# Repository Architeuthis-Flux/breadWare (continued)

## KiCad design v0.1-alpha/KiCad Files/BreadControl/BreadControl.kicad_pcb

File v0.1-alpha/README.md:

# breadWare v0.1

Hey guys, here's the PCB layout for the switch matrix board. Those holes should line up with the columns on a breadboard so this whole thing can be soldered directly onto the bottom. I just ordered 10 of these boards (in red soldermask! I've never been patient enough to wait the extra 24-48 hours to do a color other than green) so we can put a few together (I can teach whoever's interested how to hot air solder these surface mount parts) and then get on making those header pins on the sides move the correct number of electrons to make this thing work.

#
 
That white rectangle is roughly the size of a breadboard. We might be able to get the size down if we use [TQFP](https://en.wikipedia.org/wiki/Quad_flat_package) instead of these huge [PLCC](https://en.wikipedia.org/wiki/Chip_carrier#Plastic-leaded_chip_carrier) sockets. Also could someone who reads chinese look through [this datasheet](https://datasheet.lcsc.com/szlcsc/Jiangsu-Qin-Heng-CH446Q_C109471.pdf) for the [CH446Q](http://www.wch-ic.com/products/CH446.html) and tell me if there are any significant differences from [MT8816](http://images.100y.com.tw/pdf_file/41-ZARLINK-MT8816.pdf) that we're using? Because the [JLCPCB](https://jlcpcb.com/) (who is making these boards for us) has the CH446Q in stock and they'll make the board and then solder them on so we can just order fully assembled boards ridiculously cheap (and the chips themselves are ~$1, so like a quarter of the price.)

#
 
Notice how some of the pads in the middle (Plated Through Holes or PTH is the correct term just so you know) are more square and others are rounded. The squarer ones means that that pin is connected to the headers on the sides, so it can be used for measurement or power or whatever we decide when we make the control board. Those pins are: 0,1,8,16,24,31,32,40,48,56,63 which is the Y0 pin on each chip plus the ones that end up on the edges of the breadboard (31,63) and 1 because I had an extra header pin available. 
Pin 0 is connected to the Negative rail on the top of the breadboard, 31 is the top Positive rail, 32 is the bottom Negaitve rail, and 63 is the bottom Positive rail. Everything else is where you'd expect it to be.

#
 
Yes, these pin headers are on the wrong side but I'm not gonna let some stupid auto-generated 3D model tell me which side to solder them on. I might spend some time finding the 3D models for the PLCC sockets and a breadboard so this looks closer to the real thing.
Also, notice the silkscreened lines on the top and bottom are just a bit off from the holes, turns out the power rails on a breadboard arent spaced perfectly on the same grid as the rest of the pins. The line is marked where it would be if the universe made any sense.

#
 
Those letters along the middle correspond to the row labels on a breadboard.

#
  
Here's a zoomed out view of the whole schematic, those blue lines are busses, so they're actually 4 wires bundled together to make it look less messy. This is following JJ's brilliant idea for how to connect everything except I looped the ends back around so they conceptually should be thought of as a ring, If someone wants to map that out on one of those [Ring Lattice Graphs](https://i.imgur.com/oiiyKlz.png), it might make all this easier to visualize.

#

On the left we have the address lines, control lines and power input. Except for the last three with numbers, these are connected to all 8 chips together, so to make just the one we want to control do stuff, we use the Chip Select lines on the right side (labeled CS_A-H) which are wired to each chip individually. If the CS is logic 0 (~0 Volts, LOW, whatever), that chip will ignore everything that's put on the address and control lines because that signal isn't meant for it and these chips ain't no eavesdroppin' bitches. (just for everyone's learning, Chip Select lines seem to almost always be Active Low, meaning they'll ignore everything when that pin is held at logic 1 (5V or 3.3V depending on the chip) which is denoted with a line above, C̅S̅ (or /CS because overlining text is a pain in the ass on a computer. and it's typically spoken as "bar", so "CS Bar" in this case) this chip is unusual because it's Active High.)

#
 
Here's a zoomed part so you can see how I named these interconnects, it goes Pin Name (X0, X1, etc.) then the letters of the two chips it's connecting (in alpabetical order). So the pin labeled X0CD connects pin X0 on chip C to pin X0 on chip D. I had to do this like 5 times to get the wires to always connect to the same pin on both chips, but it should make the software much easier to deal with. 

#
  
Here's the table I used to figure out which chips are connected where, and this helped me put them all in alphabetical order (because I can't tell you if F is before or after H without singing the alpabet song in my head every time) so the labels are the same on both sides of the wire. Each chip is connected the to the two before and after it. 

#
One day we will have this piece of paper framed and signed by JJ.

Here are some pictures of both boards after assembly:

That green board hanging off is 2 charge pumps in parallel (for added current handling, but it was probably unnecessary) and an LM337 Negative Voltage Regulator. I built that because the power rails weren't working until I realized I swapped Vss and Vee.

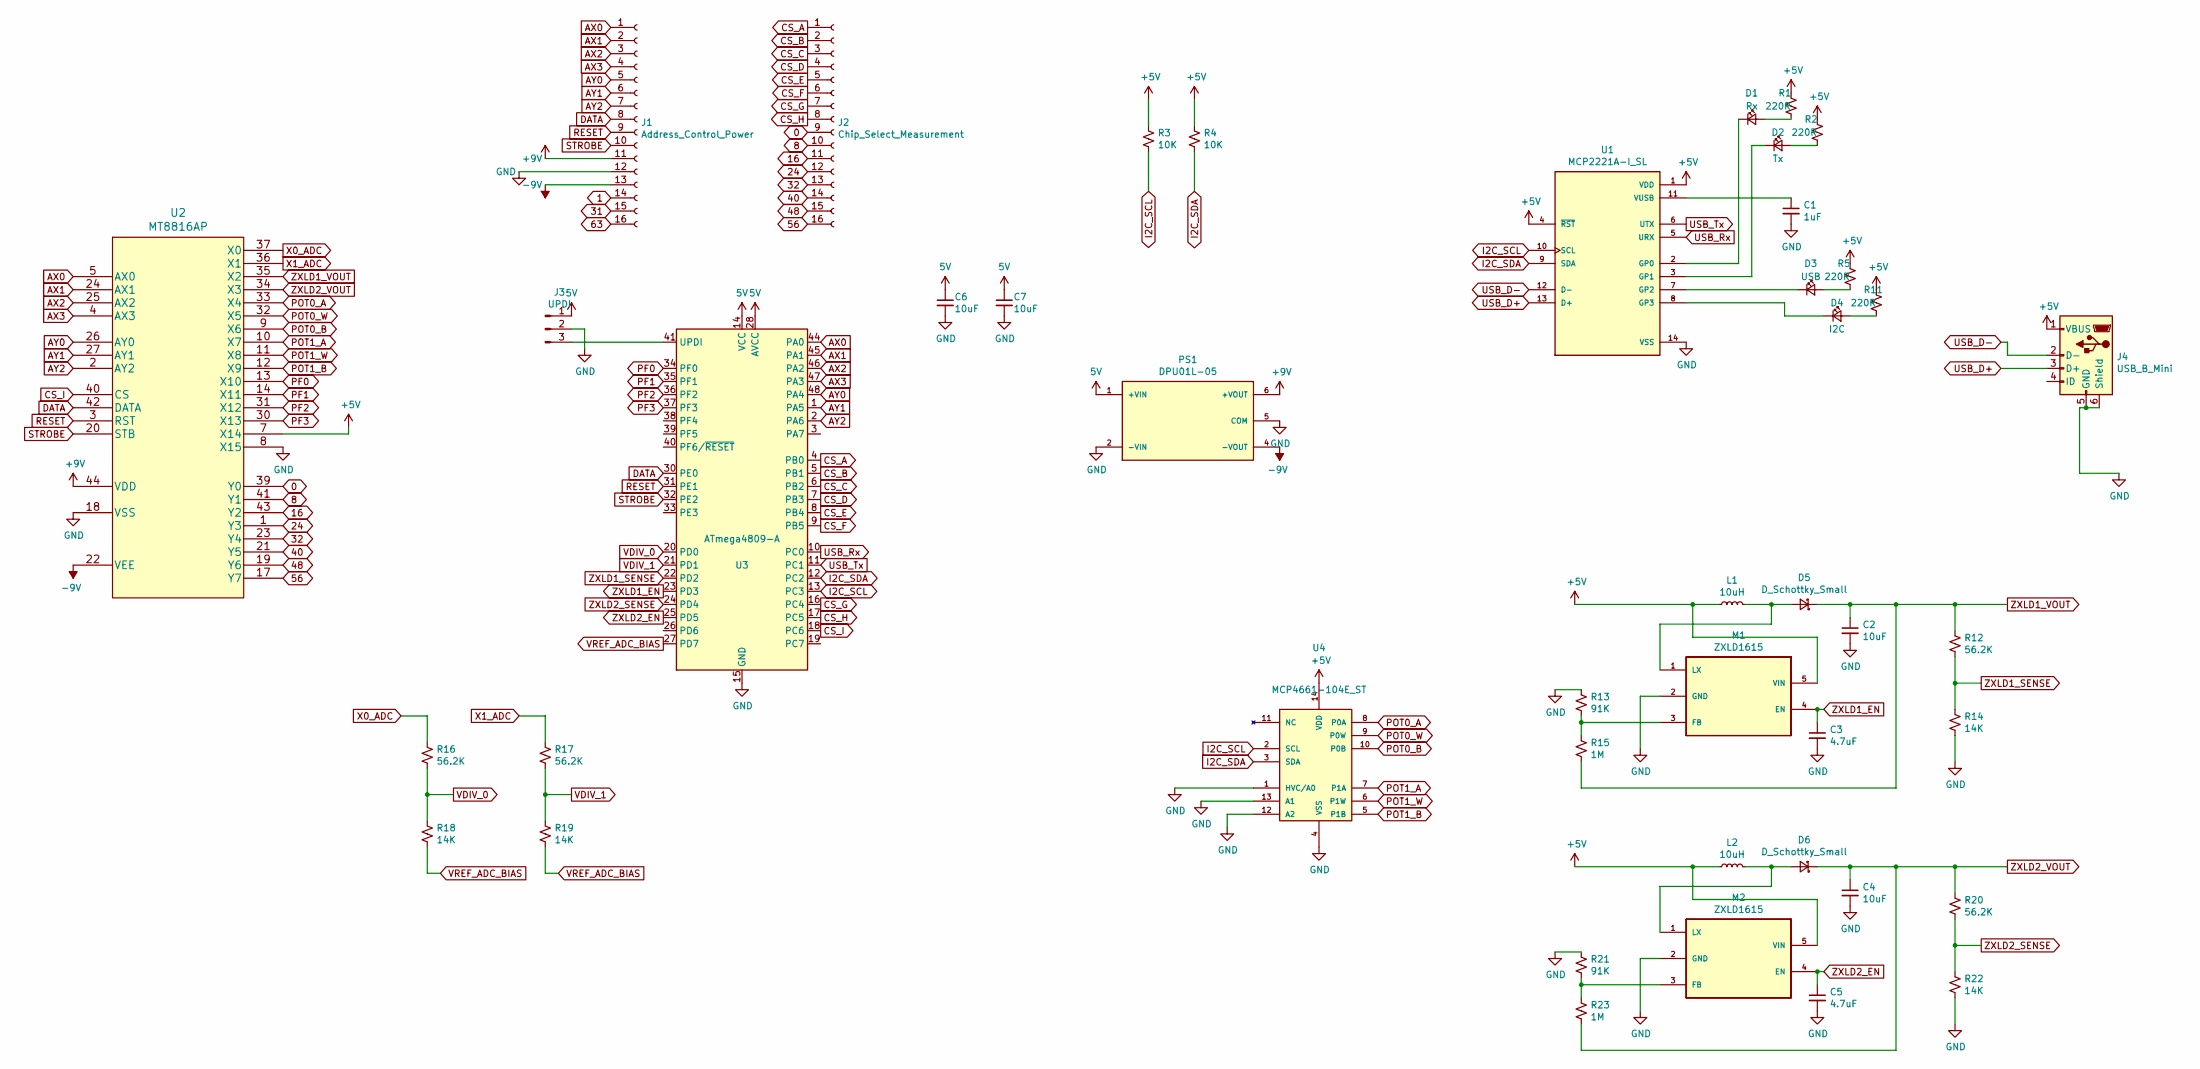
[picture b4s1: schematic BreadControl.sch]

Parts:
C1: 1uF; C_0805_2012Metric_Pad1.15x1.40mm_HandSolder
C2, C4, C6, C7: 10uF; C_0805_2012Metric_Pad1.15x1.40mm_HandSolder
C3, C5: 4.7uF; C_0805_2012Metric_Pad1.15x1.40mm_HandSolder
D1: Rx; D_0603_1608Metric_Pad1.05x0.95mm_HandSolder
D2: Tx; D_0603_1608Metric_Pad1.05x0.95mm_HandSolder
D3: USB; D_0603_1608Metric_Pad1.05x0.95mm_HandSolder
D4: I2C; D_0603_1608Metric_Pad1.05x0.95mm_HandSolder
D5, D6: D_Schottky_Small; D_SOD-323_HandSoldering
J1: Address_Control_Power; PinHeader_1x16_P2.54mm_Vertical
J2: Chip_Select_Measurement; PinHeader_1x16_P2.54mm_Vertical
J3: UPDI; PinHeader_1x03_P2.54mm_Vertical
J4: USB_B_Mini; AMPHENOL_10033526-N3212LF
L1, L2: 10uH; L_1008_2520Metric
M1, M2: ZXLD1615; SOT-23-5_HandSoldering
PS1: DPU01L-05; CONV_DPU01L-05; PARTREV 2017-03-06
R1, R2, R5, R11: 220R; R_0805_2012Metric_Pad1.15x1.40mm_HandSolder
R3, R4: 10K; R_0805_2012Metric_Pad1.15x1.40mm_HandSolder
R12, R16, R17, R20: 56.2K; R_0805_2012Metric_Pad1.15x1.40mm_HandSolder
R13, R21: 91K; R_0805_2012Metric_Pad1.15x1.40mm_HandSolder
R14, R18, R19, R22: 14K; R_0805_2012Metric_Pad1.15x1.40mm_HandSolder
R15, R23: 1M; R_0805_2012Metric_Pad1.15x1.40mm_HandSolder
U1: MCP2221A-I_SL; SOIC-14_3.9x8.7mm_P1.27mm
U2: MT8816AP; PLCC-44_16.6x16.6mm_P1.27mm
U3: ATmega4809-A; TQFP-48_7x7mm_P0.5mm
U4: MCP4661-104E_ST; TSSOP-14_4.4x5mm_P0.65mm; MPN MCP4661-104E/ST

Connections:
0: J2.9, U2.39 (Y0)
1: J1.14
8: J2.10, U2.41 (Y1)
16: J2.11, U2.43 (Y2)
24: J2.12, U2.1 (Y3)
31: J1.15
32: J2.13, U2.23 (Y4)
40: J2.14, U2.21 (Y5)
48: J2.15, U2.19 (Y6)
56: J2.16, U2.17 (Y7)
63: J1.16
+9V: J1.11, PS1.6 (+VOUT), U2.44 (VDD)
-9V: J1.13, PS1.4 (-VOUT), U2.22 (VEE)
AX0: J1.1, U2.5 (AX0), U3.44 (PA0)
AX1: J1.2, U2.24 (AX1), U3.45 (PA1)
AX2: J1.3, U2.25 (AX2), U3.46 (PA2)
AX3: J1.4, U2.4 (AX3), U3.47 (PA3)
AY0: J1.5, U2.26 (AY0), U3.48 (PA4)
AY1: J1.6, U2.27 (AY1), U3.1 (PA5)
AY2: J1.7, U2.2 (AY2), U3.2 (PA6)
CS_A: J2.1, U3.4 (PB0)
CS_B: J2.2, U3.5 (PB1)
CS_C: J2.3, U3.6 (PB2)
CS_D: J2.4, U3.7 (PB3)
CS_E: J2.5, U3.8 (PB4)
CS_F: J2.6, U3.9 (PB5)
CS_G: J2.7, U3.16 (PC4)
CS_H: J2.8, U3.17 (PC5)
CS_I: U2.40 (CS), U3.18 (PC6)
DATA: J1.8, U2.42 (DATA), U3.30 (PE0)
GND: C1.2, C2.2, C3.2, C4.2, C5.2, C6.2, C7.2, J1.12, J3.2, J4.5 (GND), J4.6 (Shield), M1.2 (GND), M2.2 (GND), PS1.2 (-VIN), PS1.5 (COM), R13.1, R14.2, R21.1, R22.2, U1.14 (VSS), U2.8 (X15), U2.18 (VSS), U3.15 (GND), U3.29 (GND), U3.43 (GND), U4.1 (HVC/A0), U4.4 (VSS), U4.12 (A2), U4.13 (A1)
I2C_SCL: R3.2, U1.10 (SCL), U3.13 (PC3), U4.2 (SCL)
I2C_SDA: R4.2, U1.9 (SDA), U3.12 (PC2), U4.3 (SDA)
unnamed: C1.1, U1.11 (VUSB)
unnamed: D1.1 (K), U1.2 (GP0)
unnamed: D1.2 (A), R1.2
unnamed: D2.1 (K), U1.3 (GP1)
unnamed: D2.2 (A), R2.2
unnamed: D3.1 (K), U1.7 (GP2)
unnamed: D3.2 (A), R5.2
unnamed: D4.1 (K), U1.8 (GP3)
unnamed: D4.2 (A), R11.2
unnamed: D5.2 (A), L1.2, M1.1 (LX)
unnamed: D6.2 (A), L2.2, M2.1 (LX)
unnamed: J3.3, U3.41 (UPDI)
unnamed: M1.3 (FB), R13.2, R15.1
unnamed: M2.3 (FB), R21.2, R23.1
PF0: U2.13 (X10), U3.34 (PF0)
PF1: U2.14 (X11), U3.35 (PF1)
PF2: U2.31 (X12), U3.36 (PF2)
PF3: U2.30 (X13), U3.37 (PF3)
POT0_A: U2.33 (X4), U4.8 (P0A)
POT0_B: U2.9 (X6), U4.10 (P0B)
POT0_W: U2.32 (X5), U4.9 (P0W)
POT1_A: U2.10 (X7), U4.7 (P1A)
POT1_B: U2.12 (X9), U4.5 (P1B)
POT1_W: U2.11 (X8), U4.6 (P1W)
RESET: J1.9, U2.3 (RST), U3.31 (PE1)
STROBE: J1.10, U2.20 (STB), U3.32 (PE2)
USB_D+: J4.3 (D+), U1.13 (D+)
USB_D-: J4.2 (D-), U1.12 (D-)
USB_Rx: U1.5 (URX), U3.10 (PC0)
USB_Tx: U1.6 (UTX), U3.11 (PC1)
VDIV_0: R16.2, R18.1, U3.20 (PD0)
VDIV_1: R17.2, R19.1, U3.21 (PD1)
VREF_ADC_BIAS: R18.2, R19.2, U3.27 (PD7)
X0_ADC: R16.1, U2.37 (X0)
X1_ADC: R17.1, U2.36 (X1)
ZXLD1_EN: C3.1, M1.4 (EN), U3.23 (PD3)
ZXLD1_SENSE: R12.2, R14.1, U3.22 (PD2)
ZXLD1_VOUT: C2.1, D5.1 (K), R12.1, R15.2, U2.35 (X2)
ZXLD2_EN: C5.1, M2.4 (EN), U3.25 (PD5)
ZXLD2_SENSE: R20.2, R22.1, U3.24 (PD4)
ZXLD2_VOUT: C4.1, D6.1 (K), R20.1, R23.2, U2.34 (X3)

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
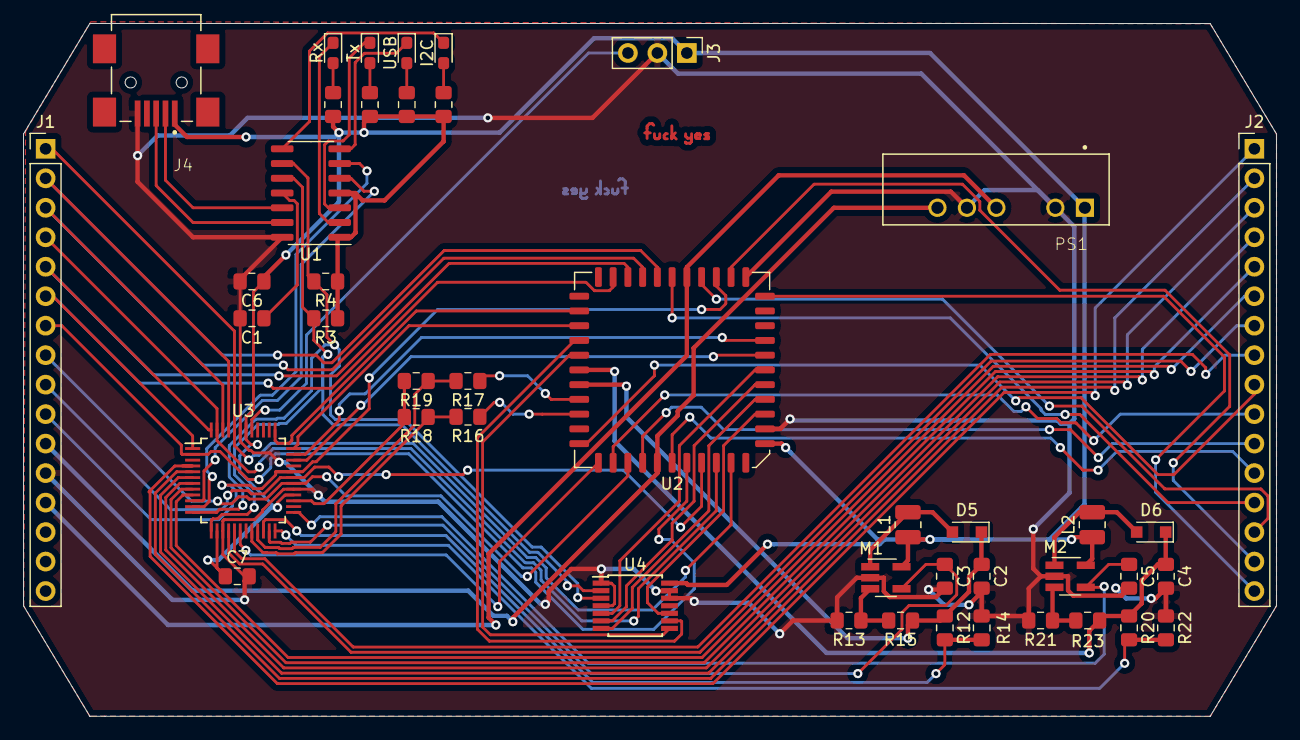
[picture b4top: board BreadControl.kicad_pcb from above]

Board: 2 copper layers, 108.0 x 59.7 mm, 44 parts (0 on the bottom side), 72 nets.

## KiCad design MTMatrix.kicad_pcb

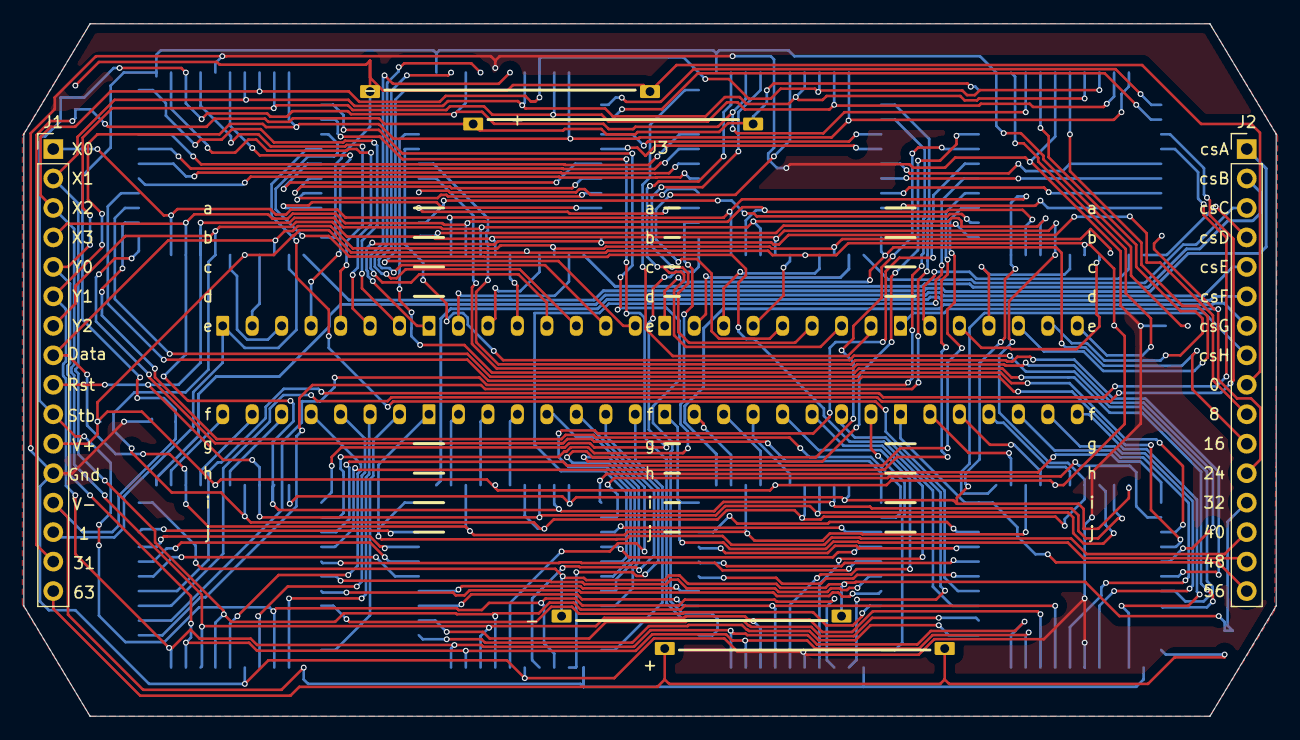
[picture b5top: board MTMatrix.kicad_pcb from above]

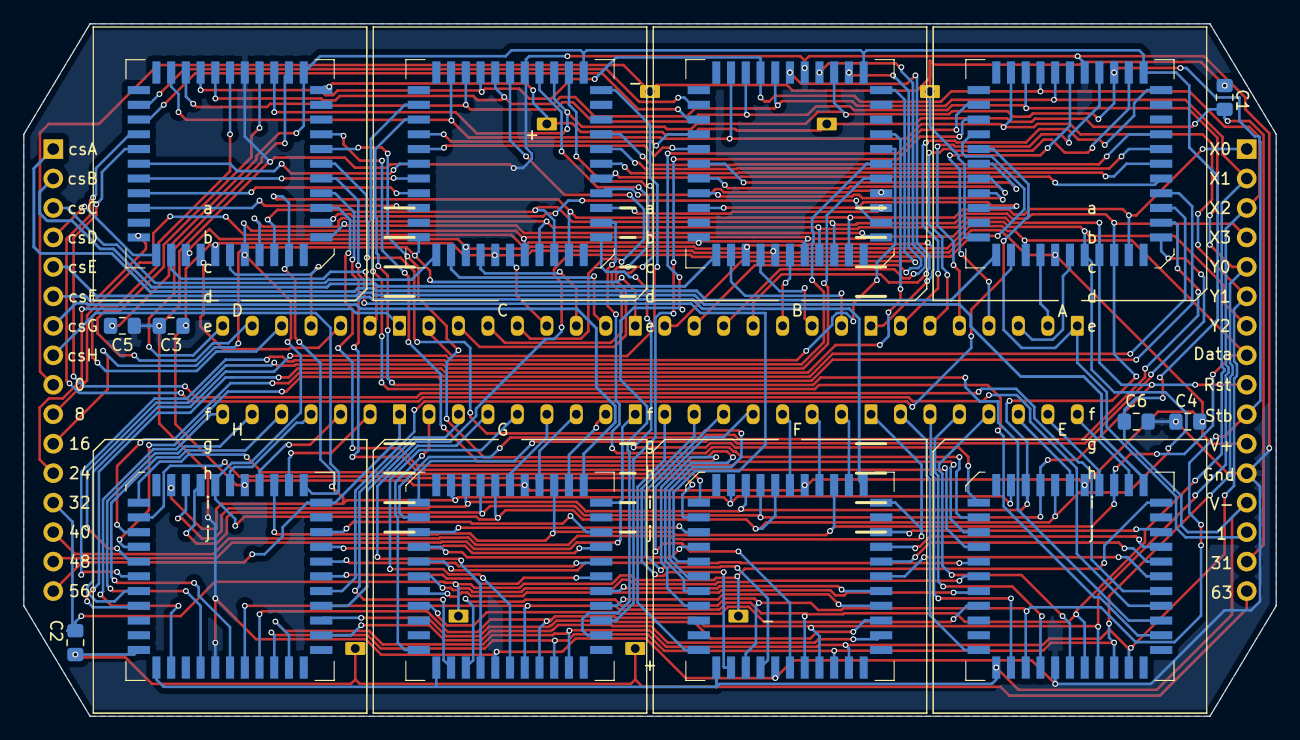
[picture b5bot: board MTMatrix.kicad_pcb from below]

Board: 2 copper layers, 107.9 x 59.7 mm, 17 parts (14 on the bottom side), 149 nets.

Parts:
A: MT8816AP; PLCC-44_SMD-Socket
B: MT8816AP; PLCC-44_SMD-Socket
C: MT8816AP; PLCC-44_SMD-Socket
C1, C2, C3, C4, C5, C6: 10uF; C_0805_2012Metric_Pad1.15x1.40mm_HandSolder
D: MT8816AP; PLCC-44_SMD-Socket
E: MT8816AP; PLCC-44_SMD-Socket
F: MT8816AP; PLCC-44_SMD-Socket
G: MT8816AP; PLCC-44_SMD-Socket
H: MT8816AP; PLCC-44_SMD-Socket
J1: Address_Control_Power; PinHeader_1x16_P2.54mm_Vertical
J2: Chip_Select_Measurement; PinHeader_1x16_P2.54mm_Vertical
J3: Breadboard; Breadboard_Top

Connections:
0: A.39, C1.2, J2.9, J3.0
1: A.41, J1.14, J3.1
2: A.43, J3.2
3: A.1, J3.3
4: A.23, J3.4
5: A.21, J3.5
6: A.19, J3.6
7: A.17, J3.7
8: B.39, J2.10, J3.8
9: B.41, J3.9
10: B.43, J3.10
11: B.1, J3.11
12: B.23, J3.12
13: B.21, J3.13
14: B.19, J3.14
15: B.17, J3.15
16: C.39, J2.11, J3.16
17: C.41, J3.17
18: C.43, J3.18
19: C.1, J3.19
20: C.23, J3.20
21: C.21, J3.21
22: C.19, J3.22
23: C.17, J3.23
24: D.39, J2.12, J3.24
25: D.41, J3.25
26: D.43, J3.26
27: D.1, J3.27
28: D.23, J3.28
29: D.21, J3.29
30: D.19, J3.30
31: C1.1, D.17, J1.15, J3.31
32: C2.2, E.39, J2.13, J3.32
33: E.41, J3.33
34: E.43, J3.34
35: E.1, J3.35
36: E.23, J3.36
37: E.21, J3.37
38: E.19, J3.38
39: E.17, J3.39
40: F.39, J2.14, J3.40
41: F.41, J3.41
42: F.43, J3.42
43: F.1, J3.43
44: F.23, J3.44
45: F.21, J3.45
46: F.19, J3.46
47: F.17, J3.47
48: G.39, J2.15, J3.48
49: G.41, J3.49
50: G.43, J3.50
51: G.1, J3.51
52: G.23, J3.52
53: G.21, J3.53
54: G.19, J3.54
55: G.17, J3.55
56: H.39, J2.16, J3.56
57: H.41, J3.57
58: H.43, J3.58
59: H.1, J3.59
60: H.23, J3.60
61: H.21, J3.61
62: H.19, J3.62
63: C2.1, H.17, J1.16, J3.63
+9V: A.44, B.44, C.44, C3.1, C4.1, D.44, E.44, F.44, G.44, H.44, J1.11
-9V: A.18, B.18, C.18, C5.2, C6.2, D.18, E.18, F.18, G.18, H.18, J1.13
/X0AB: A.37, B.37
/X0CD: C.37, D.37
/X0EF: E.37, F.37
/X0GH: G.37, H.37
/X1AB: A.36, B.36
/X1CD: C.36, D.36
/X1EF: E.36, F.36
/X1GH: G.36, H.36
/X2AB: A.35, B.35
/X2CD: C.35, D.35
/X2EF: E.35, F.35
/X2GH: G.35, H.35
/X3AB: A.34, B.34
/X3CD: C.34, D.34
/X3EF: E.34, F.34
/X3GH: G.34, H.34
/X4AH: A.33, H.33
/X4BC: B.33, C.33
/X4DE: D.33, E.33
/X4FG: F.33, G.33
/X5AH: A.32, H.32
/X5BC: B.32, C.32
/X5DE: D.32, E.32
/X5FG: F.32, G.32
/X6AH: A.9, H.9
/X6BC: B.9, C.9
/X6DE: D.9, E.9
/X6FG: F.9, G.9
/X7AH: A.10, H.10
/X7BC: B.10, C.10
/X7DE: D.10, E.10
/X7FG: F.10, G.10
/X8AC: A.11, C.11
/X8BH: B.11, H.11
/X8DF: D.11, F.11
/X8EG: E.11, G.11
/X9AC: A.12, C.12
/X9BH: B.12, H.12
/X9DF: D.12, F.12
/X9EG: E.12, G.12
/X10AC: A.13, C.13
/X10BH: B.13, H.13
/X10DF: D.13, F.13
/X10EG: E.13, G.13
/X11AC: A.14, C.14
/X11BH: B.14, H.14
/X11DF: D.14, F.14
/X11EG: E.14, G.14
/X12AG: A.31, G.31
/X12BD: B.31, D.31
/X12CE: C.31, E.31
/X12FH: F.31, H.31
/X13AG: A.30, G.30
/X13BD: B.30, D.30
/X13CE: C.30, E.30
/X13FH: F.30, H.30
/X14AG: A.7, G.7
/X14BD: B.7, D.7
/X14CE: C.7, E.7
/X14FH: F.7, H.7
/X15AG: A.8, G.8
/X15BD: B.8, D.8
/X15CE: C.8, E.8
/X15FH: F.8, H.8
AX0: A.5, B.5, C.5, D.5, E.5, F.5, G.5, H.5, J1.1
AX1: A.24, B.24, C.24, D.24, E.24, F.24, G.24, H.24, J1.2
AX2: A.25, B.25, C.25, D.25, E.25, F.25, G.25, H.25, J1.3
AX3: A.4, B.4, C.4, D.4, E.4, F.4, G.4, H.4, J1.4
AY0: A.26, B.26, C.26, D.26, E.26, F.26, G.26, H.26, J1.5
AY1: A.27, B.27, C.27, D.27, E.27, F.27, G.27, H.27, J1.6
AY2: A.2, B.2, C.2, D.2, E.2, F.2, G.2, H.2, J1.7
CS_A: A.40, J2.1
CS_B: B.40, J2.2
CS_C: C.40, J2.3
CS_D: D.40, J2.4
CS_E: E.40, J2.5
CS_F: F.40, J2.6
CS_G: G.40, J2.7
CS_H: H.40, J2.8
DATA: A.42, B.42, C.42, D.42, E.42, F.42, G.42, H.42, J1.8
GND: A.22, B.22, C.22, C3.2, C4.2, C5.1, C6.1, D.22, E.22, F.22, G.22, H.22, J1.12
RESET: A.3, B.3, C.3, D.3, E.3, F.3, G.3, H.3, J1.9
STROBE: A.20, B.20, C.20, D.20, E.20, F.20, G.20, H.20, J1.10

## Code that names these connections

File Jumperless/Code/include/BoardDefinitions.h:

//#define Serial
#define CHIP_A 0
#define CHIP_B 1
#define CHIP_C 2
#define CHIP_D 3
#define CHIP_E 4
#define CHIP_F 5
#define CHIP_G 6
#define CHIP_H 7
#define CHIP_I 8
#define CHIP_J 9

#define UNCONN_A 0
#define UNCONN_D 31
#define UNCONN_E 63
#define UNCONN_H 32

#define CS_A PIN_PG0
#define CS_B PIN_PG1
#define CS_C PIN_PG2
#define CS_D PIN_PG3
#define CS_E PIN_PG4
#define CS_F PIN_PG5
#define CS_G PIN_PG6
#define CS_H PIN_PG7
#define CS_I PIN_PF4
#define CS_J PIN_PF5

#define DATAPIN PIN_PA4
#define RESET PIN_PA5
#define STROBE PIN_PA6

#define AX0 PIN_PB0
#define AX1 PIN_PB1
#define AX2 PIN_PB2
#define AX3 PIN_PB3

#define AY0 PIN_PB4
#define AY1 PIN_PB5
#define AY2 PIN_PB6


#define GP_PC0 PIN_PC0    //anything that starts with GP_ goes to
#define GP_PC1 PIN_PC1    //the matrix chip on the control board
#define GP_PC2 PIN_PC2    //for "General Purpose"
#define GP_PC3 PIN_PC3
#define GP_PC4 PIN_PC4
#define GP_PC5 PIN_PC5
#define GP_PC6 PIN_PC6

#define GP_PE0 PIN_PE0    //anything that starts with GP_ goes to
#define GP_PE1 PIN_PE1    //the matrix chip on the control board
#define GP_PE2 PIN_PE2    //for "General Purpose"
#define GP_PE3 PIN_PE3
#define GP_PE4 PIN_PE4
#define GP_PE5 PIN_PE5
#define GP_PE6 PIN_PE6
#define GP_PE7 PIN_PE7


#define PROBE_2_1 PIN_PD0    
#define PROBE_1_1 PIN_PD4    
#define PROBE_1_2 PIN_PD7     //ADC_BIAS sets the bias so you can read negative voltages


//#define USB_RX PIN_PA0
//#define USB_TX PIN_PA1

#define IN_RX PIN_PF0
#define IN_TX PIN_PF1

#define I2C_SDA PIN_PA2
#define I2C_SCL PIN_PA3

#define mcpAddress         0x2F
#define volatileWiper0     0x00
#define volatileWiper1     0x01
#define nonvolatileWiper0  0x02
#define nonvolatileWiper1  0x03
#define TCON               0x04
#define mcpSTATUS          0x05 



#define PWR_NEG_EN PIN_PE2   //senses dual power supply voltage / 5
#define PWR_LDAC PIN_PC3  //turns on dual power rails for matrix chips

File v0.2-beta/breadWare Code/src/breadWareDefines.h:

#define CHIP_A 0
#define CHIP_B 1
#define CHIP_C 2
#define CHIP_D 3
#define CHIP_E 4
#define CHIP_F 5
#define CHIP_G 6
#define CHIP_H 7
#define CHIP_I 8

#define UNCONN_A 0
#define UNCONN_D 31
#define UNCONN_E 63
#define UNCONN_H 32

#define CS_A PIN_PB0
#define CS_B PIN_PB1
#define CS_C PIN_PB2
#define CS_D PIN_PB3
#define CS_E PIN_PB4
#define CS_F PIN_PB5
#define CS_G PIN_PD4
#define CS_H PIN_PD5
#define CS_I PIN_PD6

#define DATA PIN_PE0
#define RESET PIN_PE1
#define STROBE PIN_PE2

#define AX0 PIN_PA4
#define AX1 PIN_PA5
#define AX2 PIN_PA6
#define AX3 PIN_PA7

#define AY0 PIN_PC4
#define AY1 PIN_PC5
#define AY2 PIN_PC6


#define GP_PC0 PIN_PC0    //anything that starts with GP_ goes to
#define GP_PC1 PIN_PC1    //the matrix chip on the control board
#define GP_PC2 PIN_PC2    //for "General Purpose"
#define GP_PC3 PIN_PC3

#define ADC_VDIVO PIN_PD0    //for sensing voltages (after getting voltage
#define ADC_VDIV1 PIN_PD1    //divided by 5)
#define ADC_BIAS PIN_PD7     //sets the bias so you can read negative voltages

#define PWR_NEG_EN PIN_PD2   //senses dual power supply voltage / 5
#define PWR_LDAC PIN_PD3  //turns on dual power rails for matrix chips
//#define PWR_SENSE2 PIN_PD4   //senses power supply voltage / 5
//#define PWR_ENABLE2 PIN_PD5  //turns on adjustable power supply


#define USB_RX PIN_PA0
#define USB_TX PIN_PA1

#define IN_RX PIN_PF0
#define IN_TX PIN_PF1

#define OUT_RX PIN_PF5
#define OUT_TX PIN_PF4

#define I2C_SDA PIN_PA2
#define I2C_SCL PIN_PA3

#define POT_MAX 100

#define mcpAddress         0x28
#define volatileWiper0     0x00
#define volatileWiper1     0x01
#define nonvolatileWiper0  0x02
#define nonvolatileWiper1  0x03
#define TCON               0x04
#define mcpSTATUS          0x05 


#define ADC0 0
#define ADC1 1
#define POT0_A 2
#define POT0_W 3
#define POT0_B 4
#define POT1_A 5
#define POT1_W 6
#define POT1_B 7
#define PC0 8
#define PC1 9
#define PC2 10
#define PC3 11
#define PE3 12
#define POS_TOP_MT 13
#define NEG_BOTTOM_MT 14
#define GROUND_MT 15

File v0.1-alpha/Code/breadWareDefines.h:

#define CS_A PIN_PB0
#define CS_B PIN_PB1
#define CS_C PIN_PB2
#define CS_D PIN_PB3
#define CS_E PIN_PB4
#define CS_F PIN_PB5
#define CS_G PIN_PC4
#define CS_H PIN_PC5
#define CS_I PIN_PC6

#define DATA PIN_PE0
#define RESET PIN_PE1
#define STROBE PIN_PE2

#define AX0 PIN_PA0
#define AX1 PIN_PA1
#define AX2 PIN_PA2
#define AX3 PIN_PA3

#define AY0 PIN_PA4
#define AY1 PIN_PA5
#define AY2 PIN_PA6


#define GP_PF0 PIN_PF0    //anything that starts with GP_ goes to
#define GP_PF1 PIN_PF1    //the matrix chip on the control board
#define GP_PF2 PIN_PF2    //for "General Purpose"
#define GP_PF3 PIN_PF3

#define ADC_VDIVO PIN_PD0    //for sensing voltages (after getting voltage
#define ADC_VDIV1 PIN_PD1    //divided by 5)
#define ADC_BIAS PIN_PD7     //sets the bias so you can read negative voltages

#define PWR_SENSE1 PIN_PD2   //senses dual power supply voltage / 5
#define PWR_ENABLE1 PIN_PD3  //turns on dual power rails for matrix chips
#define PWR_SENSE2 PIN_PD4   //senses power supply voltage / 5
#define PWR_ENABLE2 PIN_PD5  //turns on adjustable power supply


#define USB_RX PIN_PC0
#define USB_TX PIN_PC1

#define I2C_SDA PIN_PC2
#define I2C_SCL PIN_PC3

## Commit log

2021-06-12 early tests
2021-06-12 first PCB
2021-06-12 fix image links
2021-06-20 Create LICENSE
2021-11-22 added tons of menus and fixed shitty ones
    I originally started with the intention of just getting it to work enough to show off in the explainer video, but I accidentally made those features actually work.
2022-11-08 Add V3 stuff
2022-11-08 Add new code for the new board
2022-11-08 Create d
2022-11-08 Control board KiCAD files
2022-11-08 Added top matrix board KiCAD files
2022-11-08 Add schematics
